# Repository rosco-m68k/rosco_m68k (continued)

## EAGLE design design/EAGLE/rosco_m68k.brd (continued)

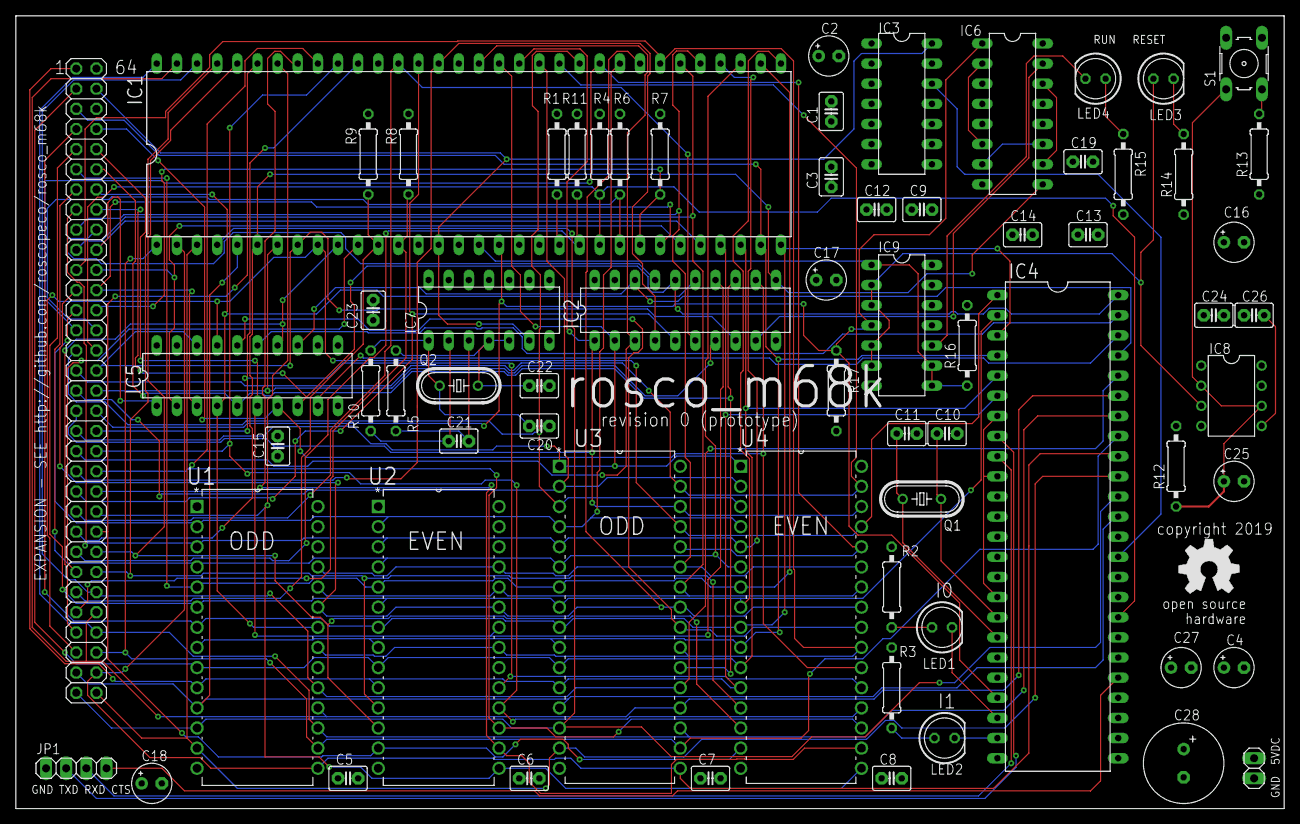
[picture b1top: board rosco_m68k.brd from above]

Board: 4 copper layers, 160.0 x 100.0 mm, 70 parts (0 on the bottom side), 96 nets.

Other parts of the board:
U$1: OSHW_8MM

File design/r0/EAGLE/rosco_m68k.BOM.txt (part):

Partlist exported from C:/Users/rosco/devel/retro/rosco_m68k/design/EAGLE/rosco_m68k.sch at 22/08/2019 15:40

Part Value          Device         Package            Description                                                                  1   2   3   4   DESCRIPTION     MF MPN            OC_FARNELL OC_NEWARK PACKAGE  POPULARITY PROG                SPICEPREFIX SUPPLIER       
C1   100nF          C2,5-3         C2.5-3             CAPACITOR                                                                                                                                                    38                                                        
C2   100uF          CPOL-EUE2.5-5  E2,5-5             POLARIZED CAPACITOR, European symbol                                                                                                                         16                             C                          
C3   100nF          C2,5-3         C2.5-3             CAPACITOR                                                                                                                                                    38                                                        
C4   100uF          CPOL-EUE2.5-5  E2,5-5             POLARIZED CAPACITOR, European symbol                                                                                                                         16                             C                          
C5   100nF          C2,5-3         C2.5-3             CAPACITOR                                                                                                                                                    38                                                        
C6   100nF          C2,5-3         C2.5-3             CAPACITOR                                                                                                                                                    38                                                        
C7   100nF          C2,5-3         C2.5-3             CAPACITOR                                                                                                                                                    38                                                        
C8   100nF          C2,5-3         C2.5-3             CAPACITOR                                                                                                                                                    38                                                        
C9   100nF          C2,5-3         C2.5-3             CAPACITOR                                                                                                                                                    38                                                        
C10  33pF           C2,5-3         C2.5-3             CAPACITOR                                                                                                                                                    38                                                        
C11  33pF           C2,5-3         C2.5-3             CAPACITOR                                                                                                                                                    38                                                        
C12  100nF          C2,5-3         C2.5-3             CAPACITOR                                                                                                                                                    38                                                        
C13  100nF          C2,5-3         C2.5-3             CAPACITOR                                                                                                                                                    38                                                        
C14  100nF          C2,5-3         C2.5-3             CAPACITOR                                                                                                                                                    38                                                        
C15  100nF          C2,5-3         C2.5-3             CAPACITOR                                                                                                                                                    38                                                        
C16  100uF          CPOL-EUE2.5-5  E2,5-5             POLARIZED CAPACITOR, European symbol                                                                                                                         16                             C                          
C17  100uF          CPOL-EUE2.5-5  E2,5-5             POLARIZED CAPACITOR, European symbol                                                                                                                         16                             C                          
C18  100uF          CPOL-EUE2.5-5  E2,5-5             POLARIZED CAPACITOR, European symbol                                                                                                                         16                             C                          
C19  100nF          C2,5-3         C2.5-3             CAPACITOR                                                                                                                                                    38                                                        
C20  22pF           C2,5-3         C2.5-3             CAPACITOR                                                                                                                                                    38                                                        
C21  100nF          C2,5-3         C2.5-3             CAPACITOR                                                                                                                                                    38                                                        
C22  22pF           C2,5-3         C2.5-3             CAPACITOR                                                                                                                                                    38                                                        
C23  100nF          C2,5-3         C2.5-3             CAPACITOR                                                                                                                                                    38                                                        
C24  100nF          C2,5-3         C2.5-3             CAPACITOR                                                                                                                                                    38                                                        
C25  100uF          CPOL-EUE2.5-5  E2,5-5             POLARIZED CAPACITOR, European symbol                                                                                                                         16                             C                          
C26  100nF          C2,5-3         C2.5-3             CAPACITOR                                                                                                                                                    38                                                        
C27  100uF          CPOL-EUE2.5-5  E2,5-5             POLARIZED CAPACITOR, European symbol                                                                                                                         16                             C                          
C28  400uF          CPOL-EUE3.5-10 E3,5-10            POLARIZED CAPACITOR, European symbol                                                                                                                         5                              C                          
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
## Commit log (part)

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2023-09-29 Fix a buffer overflow in E-Kermit GCC throws a warning/error after changing some compile settings. If `aln` >= `SIZEBUFL`, `i` will be `SIZEBUFL` at the end of the loops. `sizebuf[i] = '\0'` will the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
2023-09-29 Remove some custom recipes in stage2
2023-09-29 Clean up variables and config in makefiles Also minimize the inclusion of stage1 headers from stage2 and do some other cleanup and fixes.
2023-09-29 Duplicate variable defaults to stage2
2023-09-29 Remove configuration from `config.mk`, decouple stage2
2023-09-29 Improve Updateflash ROM ID Error Message (#362)
    * Updateflash checks that manufacturer is SST
    Ensures that the flash devices aren't mistaken for a device by another
    manufacturer which uses the same device ID.
    * Add a more helpful device message to updateflash
    Having the flash write jumper not installed will cause the ROMs not to
    be identifiable by the software, leading to an inability to program.
2023-10-09 Squashed commit of the following:
    commit 6568b6beaf75071636ffe7bb0fcaa0c35afb091f
    Author: Thomas Jager <0xTJ@users.noreply.github.com>
    Date: Fri Sep 29 13:22:30 2023 -0400
    Improve Updateflash ROM ID Error Message (#362)
    * Updateflash checks that manufacturer is SST
    Ensures that the flash devices aren't mistaken for a device by another
2023-10-09 copy sdfat_menu.bin as ROSCODE1.BIN on SD card
2023-10-09 Entrypoint is at virtual address, not load address This allows the ELF E_ENTRY to be usable, because it doesn't trigger the initial copying.
2023-10-09 Enforce physical load address in physical mode
2023-10-09 Move Kmain type definition to a header Also move some function declarations related to loading to the same header. Some more cleanup could be done in the future to reduce the number of extern variabl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
2023-10-09 Move kermit buffers to unused memory
2023-10-09 Don't hardcode SP for stage2
2023-10-09 improved method to free SERIAL port vs killall :)
2023-10-10 remove -n from macos open (accumulates terminals)
2023-10-10 Fix for _kermit_end being non-inclusive
2023-10-11 Boot ELF Kernel from Storage (#365)
    * Allow using more than the minimal FAT API
    Needed to allow seeking.
    * Allow modifying the kernel entry point during load
    * Remove duplicate define
    * Preliminary ELF loading
    Seems to work, as long as the ELF file to load doesn't have segments
2023-10-22 Roll 2.5.dev
2023-10-22 Roll 2.5.dev release (#370)
2023-10-24 Ignore static libs
2023-10-24 Add <vector> include
2023-10-24 Revert "🤷 Try fix GITHUB_WORKSPACE thing [3]"
    This reverts commit 4369599145c125a8a3ae4daa409131a3e2088630.
2023-10-24 Test in CI, take 2 🤞
2023-10-26 Make program responsible for pmm setup
2023-10-27 Don't use impl-reserved ids
2023-10-28 Remove revision-specific defines from public Except for MFP, which is the only place that IOBASE was actually used
2023-10-28 Cleanup Outdated Equates (#377)
    * Remove equates.S
    * Remove revision-specific defines from public
    Except for MFP, which is the only place that IOBASE was actually used
    * Fix comment about equates.S
2023-10-28 Add CRC7 and 16 to SD Card routines
2023-10-29 Get it kinda working
2023-10-29 Handle TRAP15 the same as TRAP1
2023-10-29 Initial work on ctrl-c break into program
2023-10-29 fix frame struct refactor snafu
2023-10-29 More tidying up, still not figured out rerun 😭
2023-10-29 REVERT: temp test prog
2023-10-30 Update docs a bit
2023-10-30 Maybe fix ctrl-c interrupt stack handling
2023-10-31 Fix #359 (#378)
2023-10-31 Fix issues from PR
2023-11-07 Us FSINFO hints
2023-11-11 Initial work r2030 board
2023-11-11 Use reference instead of hardcoding
2023-11-18 Update README.md (#386)
2023-11-19 Switch default CPU to 68000
2023-11-19 Don't (ab)use SDB_STATUS for BERR_HANDLER return
2023-11-19 Consistently use INSTALL_TEMP_BERR_HANDLER
2023-11-28 Update r2 to Kicad 7
2023-11-28 Complete Kicad 7 migration
2023-12-01 Update typos in documentation
2023-12-02 Feature/kicad 7 (#388)
    * Update r2 to Kicad 7
    * Update r2020 to Kicad 7
    * Complete Kicad 7 migration
2023-12-05 Cleanup
2023-12-09 Align packed structs externally
2023-12-10 Swap TX/RX & CTS/RTS silkscreen r2020
    * Swap over labels
    * Add arrows
    * Some board tidy up
2023-12-10 Silkscreen fixes to match r2/r2020
2023-12-16 We've been lucky - it won't last. Fix it 😅
2023-12-16 Feature/fix weird kermit thing (#396)
    * We've been lucky - it won't last. Fix it 😅
    * Also include header
2023-12-17 Pack nested exception structs
2023-12-17 Use a Special Temporary BERR Handler for MC68000 (#397)
    * Always use helper routines
    * Use special temporary BERR handler for MC68000
    * Fix comment typo
2023-12-17 Tidy up for fab
2023-12-20 Only use SZ strings for multi-char sequences in ANSI console
2023-12-20 Remove duplicate serial.asm Stage2 has a copy of the serial.asm file present in stage1. Stage1 only uses RECVCHAR, which has the same pattern as the FW_* routines in trap14.asm. The FW_* EFP wrappers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
2023-12-20 Allow linker to specify memory top
2023-12-28 Fix incorrect number of 4k7s
2023-12-29 Add 030 information doc
2023-12-29 Bring r2 010 docs in line with new 020 docs
2024-01-01 Ignore KiCad lock files
2024-01-01 Fix RNs in BOM
2024-01-02 Feature/r2030 (#393)
    * Ignore bak
    * Initial work r2030 board
    * Silk fixes
    * Update for proto manufacturing
    * Update to Kicad 7
    * Fix pre-prod bugs
2024-01-02 Switch to defines for check/get input
2024-01-02 Support keyboard in sdfat_menu
2024-01-02 Add basic cache control to libs
2024-01-05 Address PR comments
2024-01-07 First cut keyboard support (#398)
    * First cut keyboard support
    * Support keyboard in sdfat_menu
    * Add missing define for check input
    * Switch to defines for check/get input
    * Support keyboard in memcheck
    * Address PR comments
2024-01-07 Fix master README notice
2024-01-07 Update release version notice
2024-01-07 Bring additions to firmware linker over to 64k
2024-01-13 Fix PR comments
2024-01-14 Update README.md
    Update to reflect JLCPCB are current for commercial boards.
2024-01-14 Update README.md (#407)
    Update to reflect JLCPCB are current for commercial boards.
2024-01-14 Add keyboard docs (#406)
    * Add keyboard docs
    * Address PR comment 😊
2024-01-25 Xosera ANSI term now overloading INPUTCHAR and CHECKINPUT
2024-01-26 Disable caches on warmboot
2024-01-27 Clear caches to avoid Sofowara FaFluru
    * Will avoid serious Dvsioi bybzere errors (observed in testing)
2024-01-28 Try keyboard input
2024-02-01 Restore use of BERR_CONT_ADDR in Xosera probing for 68000 use (#412)
2024-02-05 Add keyboard manual and errata
2024-02-06 Add NOP between INITMEMCOUNT write and read
2024-02-11 Feature/keyboard commercial docs (#413)
    * Remove outdated keyboard info
    * Add keyboard manual and errata
2024-02-20 Put common ld script parts in a common file
2024-02-20 Tweak stage2 ld script
2024-02-20 Fix incorrect EFPT offset in ld script
2024-02-20 Make zip unsigned char This has no effect, but figured it made sense for predictability.
2024-02-20 Don't assume that .data LMA is right after text
2024-02-27 Round updateflash half_size up Avoid missing the last byte when programming an odd-size image
2024-03-09 Minor classic refresh for 2024
    * Add DC jack
    * Silk cleanup
    * Unify added memory expansion headers
    * Minor routing cleanup
    * QR code on silk
2024-03-10 Minor classic refresh for 2024 (#416)
    * Minor classic refresh for 2024
    * Add DC jack
    * Silk cleanup
    * Unify added memory expansion headers
    * Minor routing cleanup
    * QR code on silk
2024-03-17 Update designs for copro GAL change
2024-03-17 Re-add mistakenly-removed polarity symbols
2024-03-18 Don't put debug_dump data below SP
2024-03-18 Load debug_stub fault address according to format
2024-03-21 Write to correct registers when setting red LED
2024-03-21 Change MFP use of SDB_SYSFLAGS, don't clear pins with system-use flag cleared
2024-03-22 More address lines into GALs
2024-04-05 prod
2024-04-07 Fix #422
2024-04-07 Fix debug trap handler beyond MC68010 (#418)
    * Don't put debug_dump data below SP
    * Use A6 as pointer to exception stack frame
    * Load debug_stub fault address according to format
    * Update copyright year
    * Propagate debug_stub changes to r68k and libs
    ---------
2024-04-07 Update designators to RUN/RESET in current BOMs
2024-04-07 Remove references to 'GPIO'
2024-04-15 Mask expansion and silk tidy after first spin
2024-04-23 Use a top-level Makefile to assemble stage1 and stage2
2024-04-23 Rename stage2 entry point to STAGE2_START
2024-04-25 Move some common Makefile lines into a central shared file
2024-04-26 Undo change to CPU options
2024-05-13 Clean up included Makefiles
2024-05-13 Add GCC 14 to param=min-pagesize=0
2024-05-14 Feature/smd birdseed (#427)
    * GAL changes to better support coprocessor
    * Update designs for copro GAL change
    * Revert accidental DUARTSEL changes
    * Re-add mistakenly-removed polarity symbols
    * Tentative r2 SMD design
    * Resize tiny resistors
2024-05-20 Fix leftover D3 spur
2024-05-20 Add r2.2 docs
2024-05-20 Also update fus and jed files
2024-05-20 PR fix
2024-05-22 Fix mame target in fw
2024-06-02 Fall through in EFPT C wrappers instead of branching
2024-06-08 Link stage2 against stage1 (#432)
    * Move stage1code into subdirectory
    * Use a top-level Makefile to assemble stage1 and stage2
    * Actually link stage2 against stage1 symbols, remove duped math
    * Remove stage2/machine.asm
    * Rename stage2 entry point to STAGE2_START
    * Clean up Makefiles
2024-06-18 Update 2.2 docs
2024-06-26 Update 2.2 docs (#433)
    * Update 2.2 docs
    * Remove eliminated C16
2024-07-21 Document MAME serial terminal
2024-07-27 Document MAME serial terminal (#436)
    * Document MAME serial terminal
    * Add success image
    * PR fix
2024-08-04 Fix an issue whereby we stomped .early_data which broke character devices (#440)
2024-08-04 Pin MicroPython core to v1.23.0
2024-08-04 Switch to new toolchain
2024-08-04 Add rosco_m68k micropython port
2024-08-04 Replace FAT12 with littlefs
2024-08-04 Split romfs support out a bit, move to newlib later
2024-08-04 Hook up 720KB ROMFS for 1MB ROM
2024-08-04 Remove Xosera submodule
2024-08-04 Make menu work
2024-08-04 Fix, then deprecate, ROM kernel
2024-08-04 Don't print video banner
2024-08-04 Make it autodetect both r1 Xosera and XoseRAM
2024-08-04 Enable 5sec timer
2024-08-04 Submods in pipeline
2024-08-04 Submods in pipeline, take 2
2024-08-04 Install xxd in build
2024-08-04 Revert "Install xxd in build"
    This reverts commit 10acd52168825b3cae3ba8441ace8dd14ca9db9c.
2024-08-04 Support audio in splash
2024-08-05 Integrate Xark's rect drawing fixes
2024-08-05 Re-enable blitter wait hack for now
2024-08-07 xwait_blit_ready before touching blitter
2024-08-08 firmware/trap14.asm: Add RECVCHAR for FC == 17.
2024-08-20 PR comments
2024-08-20 Feature/concept 2.5 (#435)
    * Add micropython core
    * Pin MicroPython core to v1.23.0
    * Switch to new toolchain
    * Add micropython submodule
    * Pin MP to v1.23.0
    * Add rosco_m68k micropython port
2024-09-06 r68k firmware: added #17 INPUTCHAR and #18 CHECKINPUT (#442)
    * firmware/trap14.asm: Add RECVCHAR for FC == 17.
    * firmware/trap14.asm: fixed up comment and added FC #18.
    ---------
    Authored-by: Warren Toomey <wkt@tuhs.org>
    Approved-by: Ross Bamford <roscopeco@gmail.com>
2024-10-02 skip splash if UART A input and exit loader to kermit upload if key was `k`
2024-10-04 Docs sept2024 update
2024-10-04 Build smaller flash ROMs in CI
2024-10-05 Remove sysconfig from menus for now
2024-10-06 Add dir traversal to SD demo
2024-10-06 Add evolution
2024-10-06 Try tables?
2024-10-06 Build smaller flash ROMs in CI (#452)
    * Build smaller flash ROMs in CI
    * Fix ROMDEVICE ids :D
2024-10-08 Try change based on PR comment
2024-10-08 Fix #448 (#458)
2024-10-08 Update toolchain docs
2024-10-09 WIP: Feature/remove bare metal toolchain dependency (#454)
    * Final removal of bare-metal toolchain dependencies
    * Update toolchain docs
2024-10-11 First PoC CH559 HID
2024-10-26 MAME can't support PMOVE MMUSP, use TC instead
2024-10-26 Fix build error in libs with gcc 13 due to libm maybe-uninitialized variable (#463)
2024-12-24 Add FW_CHECKINPUT and clear input buffer before debug_stub keypress wait
2025-02-19 Remove store link
2025-03-08 Upgrade actions/upload-artifact to non-removed v4
2025-04-06 Wait for a keypress at the end of `debug_stub` (#470)
    * Call FW_INPUTCHAR at the end of debug_stub
    * Add FW_CHECKINPUT and clear input buffer before debug_stub keypress wait
2025-04-14 Properly clear long-word D0 in CPUTYPE '000 check
2025-04-25 Move ROMFS to offset 0x40000 in flash
2025-05-31 Add in getting started infor from website to readme as markdown files
2025-06-07 Fix typo in PRINTCHAR description
2025-06-07 Fix typo in PRINTCHAR description (#482)
2026-03-11 feat: adds filename option and translate to text
